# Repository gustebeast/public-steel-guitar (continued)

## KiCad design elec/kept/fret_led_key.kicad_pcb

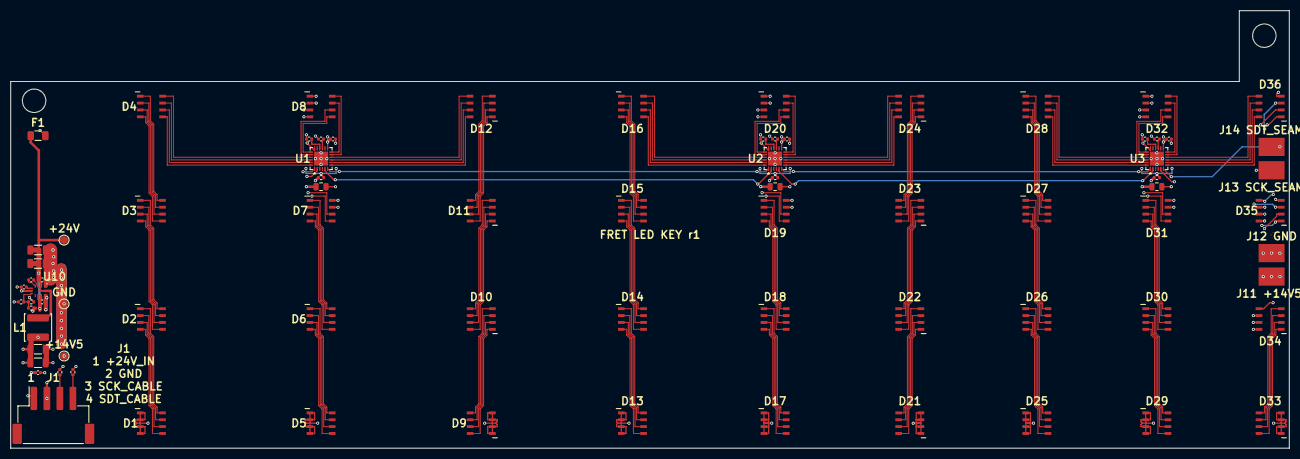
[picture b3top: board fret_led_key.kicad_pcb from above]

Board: 4 copper layers, 245.5 x 84.0 mm, 79 parts (0 on the bottom side), 171 nets.

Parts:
C1, C2, C3, C34: 1uF/25V; C_0402_1005Metric
C11, C12, C13, C32, C33, C35, C38: 100nF/50V; C_0402_1005Metric
C21, C22, C23: 4.7uF/50V; C_0805_2012Metric
C30, C31, C36, C37: 10uF/50V; C_1206_3216Metric
D1, D2, D3, D4, D5, D6, D7, D8, D9, D10, D11, D12, D13, D14, D15, D16, D17, D18, D19, D20, D21, D22, D23, D24, D25, D26, D27, D28, D29, D30, D31, D32, D33, D34, D35, D36: XL-5050RGBW; XINGLIGHT_XL-5050RGBW
F1: JFC1206-1200FS; Fuse_1206_3216Metric
J1: S4B-XH-SM4-TB; JST_XH_S4B-XH-SM4-TB_1x04-1MP_P2.50mm_Horizontal
J11, J12, J13, J14: YZF0002-38080-02; Xinyangze_YZF0002-38080-02
L1: SWPA5040S4R7MT; L_Sunlord_SWPA5040S
R1, R2, R3: 3k3; R_0402_1005Metric
R10: 100k 1%; R_0402_1005Metric
R11: 7k68 1%; R_0402_1005Metric
R12: 200k 1%; R_0402_1005Metric
R21, R22: 1k 1%; R_0402_1005Metric
R41, R42, R43: 0R; R_0402_1005Metric
TP1, TP2, TP3: TP; TestPoint_Pad_D1.5mm
U1, U2, U3: TLC5971RGER; Texas_RGE0024H_VQFN-24-1EP_4x4mm_P0.5mm_EP2.7x2.7mm
U10: LMR33630BRNXR; Texas_RNX0012_VQFN-HR-12_2x3mm_P0.5mm

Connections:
+14V5: C11.1, C12.1, C13.1, C21.1, C22.1, C23.1, C36.1, C37.1, C38.1, J11.1, L1.2, R10.1, R41.1, R42.1, R43.1, TP2.1, U1.13, U2.13, U3.13
+24V: C30.1, C31.1, C32.1, C35.1, F1.2, TP1.1, U10.2, U10.9, U10.10
+24V_IN: F1.1, J1.1
BOOT: C33.1, U10.4
BUCK_VCC: C34.1, U10.5
FB: R10.2, R11.1, R12.1, U10.7
FEED1: D1.1, D1.2, D1.3, D1.4, D5.1, D5.2, D5.3, D5.4, D9.1, D9.2, D9.3, D9.4, R41.2
FEED2: D13.1, D13.2, D13.3, D13.4, D17.1, D17.2, D17.3, D17.4, D21.1, D21.2, D21.3, D21.4, R42.2
FEED3: D25.1, D25.2, D25.3, D25.4, D29.1, D29.2, D29.3, D29.4, D33.1, D33.2, D33.3, D33.4, R43.2
GND: C1.2, C2.2, C3.2, C11.2, C12.2, C13.2, C21.2, C22.2, C23.2, C30.2, C31.2, C32.2, C34.2, C35.2, C36.2, C37.2, C38.2, J1.2, J12.1, R1.2, R2.2, R3.2, R11.2, R12.2, TP3.1, U1.18, U1.25, U2.18, U2.25, U3.18, U3.25, U10.1, U10.6, U10.11
IREF1: R1.1, U1.16
IREF2: R2.1, U2.16
IREF3: R3.1, U3.16
SCK_1: U1.5, U2.2
SCK_2: U2.5, U3.2
SCK_CABLE: J1.3, R21.1
SCK_IN: R21.2, U1.2
SCK_SEAM: J13.1, U3.5
SDT_1: U1.6, U2.1
SDT_2: U2.6, U3.1
SDT_CABLE: J1.4, R22.1
SDT_IN: R22.2, U1.1
SDT_SEAM: J14.1, U3.6
SW: C33.2, L1.1, U10.3, U10.12
VREG1: C1.1, U1.15
VREG2: C2.1, U2.15
VREG3: C3.1, U3.15
Z1_B_0: D1.7, D2.3
Z1_B_1: D2.7, D3.3
Z1_B_2: D3.7, D4.3
Z1_B_RET: D4.7, U1.23
Z1_G_0: D1.6, D2.2
Z1_G_1: D2.6, D3.2
Z1_G_2: D3.6, D4.2
Z1_G_RET: D4.6, U1.22
Z1_R_0: D1.5, D2.1
Z1_R_1: D2.5, D3.1
Z1_R_2: D3.5, D4.1
Z1_R_RET: D4.5, U1.21
Z1_W_0: D1.8, D2.4
Z1_W_1: D2.8, D3.4
Z1_W_2: D3.8, D4.4
Z1_W_RET: D4.8, U1.24
Z2_B_0: D5.7, D6.3
Z2_B_1: D6.7, D7.3
Z2_B_2: D7.7, D8.3
Z2_B_RET: D8.7, U1.20
Z2_G_0: D5.6, D6.2
Z2_G_1: D6.6, D7.2
Z2_G_2: D7.6, D8.2
Z2_G_RET: D8.6, U1.12
Z2_R_0: D5.5, D6.1
Z2_R_1: D6.5, D7.1
Z2_R_2: D7.5, D8.1
Z2_R_RET: D8.5, U1.11
Z2_W_0: D5.8, D6.4
Z2_W_1: D6.8, D7.4
Z2_W_2: D7.8, D8.4
Z2_W_RET: D8.8, U1.19
Z3_B_0: D9.7, D10.3
Z3_B_1: D10.7, D11.3
Z3_B_2: D11.7, D12.3
Z3_B_RET: D12.7, U1.9
Z3_G_0: D9.6, D10.2
Z3_G_1: D10.6, D11.2
Z3_G_2: D11.6, D12.2
Z3_G_RET: D12.6, U1.8
Z3_R_0: D9.5, D10.1
Z3_R_1: D10.5, D11.1
Z3_R_2: D11.5, D12.1
Z3_R_RET: D12.5, U1.7
Z3_W_0: D9.8, D10.4
Z3_W_1: D10.8, D11.4
Z3_W_2: D11.8, D12.4
Z3_W_RET: D12.8, U1.10
Z4_B_0: D13.7, D14.3
Z4_B_1: D14.7, D15.3
Z4_B_2: D15.7, D16.3
Z4_B_RET: D16.7, U2.23
Z4_G_0: D13.6, D14.2
Z4_G_1: D14.6, D15.2
Z4_G_2: D15.6, D16.2
Z4_G_RET: D16.6, U2.22
Z4_R_0: D13.5, D14.1
Z4_R_1: D14.5, D15.1
Z4_R_2: D15.5, D16.1
Z4_R_RET: D16.5, U2.21
Z4_W_0: D13.8, D14.4
Z4_W_1: D14.8, D15.4
Z4_W_2: D15.8, D16.4
Z4_W_RET: D16.8, U2.24
Z5_B_0: D17.7, D18.3
Z5_B_1: D18.7, D19.3
Z5_B_2: D19.7, D20.3
Z5_B_RET: D20.7, U2.20
Z5_G_0: D17.6, D18.2
Z5_G_1: D18.6, D19.2
Z5_G_2: D19.6, D20.2
Z5_G_RET: D20.6, U2.12
Z5_R_0: D17.5, D18.1
Z5_R_1: D18.5, D19.1
Z5_R_2: D19.5, D20.1
Z5_R_RET: D20.5, U2.11
Z5_W_0: D17.8, D18.4
Z5_W_1: D18.8, D19.4
Z5_W_2: D19.8, D20.4
Z5_W_RET: D20.8, U2.19
Z6_B_0: D21.7, D22.3
Z6_B_1: D22.7, D23.3
Z6_B_2: D23.7, D24.3
Z6_B_RET: D24.7, U2.9
Z6_G_0: D21.6, D22.2
Z6_G_1: D22.6, D23.2
Z6_G_2: D23.6, D24.2
Z6_G_RET: D24.6, U2.8
Z6_R_0: D21.5, D22.1
Z6_R_1: D22.5, D23.1
Z6_R_2: D23.5, D24.1
Z6_R_RET: D24.5, U2.7
Z6_W_0: D21.8, D22.4
Z6_W_1: D22.8, D23.4
Z6_W_2: D23.8, D24.4
Z6_W_RET: D24.8, U2.10
Z7_B_0: D25.7, D26.3
Z7_B_1: D26.7, D27.3
Z7_B_2: D27.7, D28.3
Z7_B_RET: D28.7, U3.23
Z7_G_0: D25.6, D26.2
Z7_G_1: D26.6, D27.2
Z7_G_2: D27.6, D28.2
Z7_G_RET: D28.6, U3.22
Z7_R_0: D25.5, D26.1
Z7_R_1: D26.5, D27.1
Z7_R_2: D27.5, D28.1
Z7_R_RET: D28.5, U3.21
Z7_W_0: D25.8, D26.4
Z7_W_1: D26.8, D27.4
Z7_W_2: D27.8, D28.4
Z7_W_RET: D28.8, U3.24
Z8_B_0: D29.7, D30.3
Z8_B_1: D30.7, D31.3
Z8_B_2: D31.7, D32.3
Z8_B_RET: D32.7, U3.20
Z8_G_0: D29.6, D30.2
Z8_G_1: D30.6, D31.2
Z8_G_2: D31.6, D32.2
Z8_G_RET: D32.6, U3.12
Z8_R_0: D29.5, D30.1
Z8_R_1: D30.5, D31.1
Z8_R_2: D31.5, D32.1
Z8_R_RET: D32.5, U3.11
Z8_W_0: D29.8, D30.4
Z8_W_1: D30.8, D31.4
Z8_W_2: D31.8, D32.4
Z8_W_RET: D32.8, U3.19
Z9_B_0: D33.7, D34.3
Z9_B_1: D34.7, D35.3
Z9_B_2: D35.7, D36.3
Z9_B_RET: D36.7, U3.9
Z9_G_0: D33.6, D34.2
Z9_G_1: D34.6, D35.2
Z9_G_2: D35.6, D36.2
Z9_G_RET: D36.6, U3.8
Z9_R_0: D33.5, D34.1
Z9_R_1: D34.5, D35.1
Z9_R_2: D35.5, D36.1
Z9_R_RET: D36.5, U3.7
Z9_W_0: D33.8, D34.4
Z9_W_1: D34.8, D35.4
Z9_W_2: D35.8, D36.4
Z9_W_RET: D36.8, U3.10

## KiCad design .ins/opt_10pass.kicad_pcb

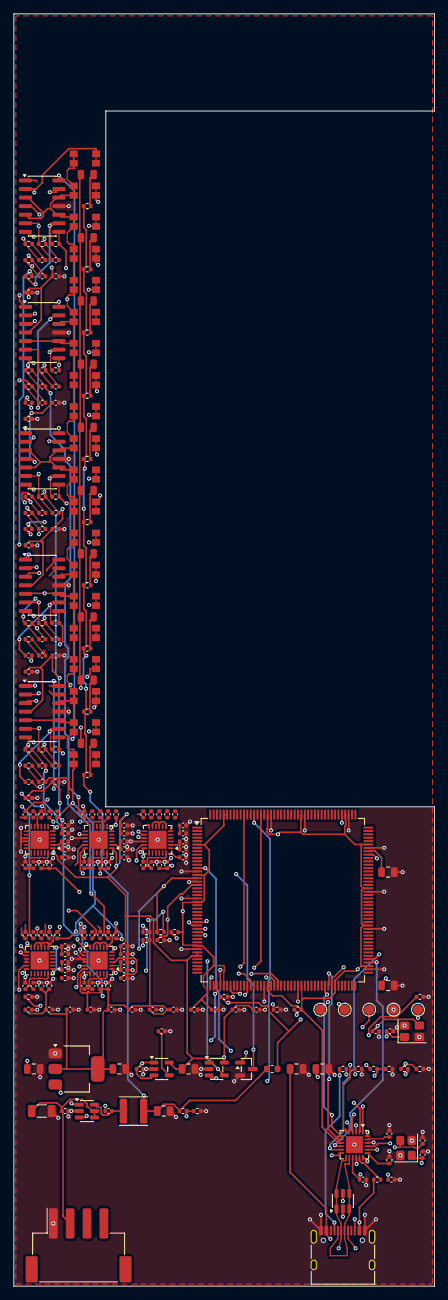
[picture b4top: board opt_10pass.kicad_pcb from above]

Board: 4 copper layers, 62.3 x 188.5 mm, 241 parts (0 on the bottom side), 148 nets.

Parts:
C100, C101, C102, C103, C104, C105, C106, C107, C108, C109, C110, C111, C121, C140, C141, C142, C143, C161, C163: 100nF; C_0402_1005Metric
C112, C113: 2.2uF; C_0805_2012Metric
C120, C122, C127: 1uF; C_0402_1005Metric
C123, C124: 27pF; C_0402_1005Metric
C125, C126: 30pF; C_0402_1005Metric
C130: 100nF; C_0805_2012Metric
C131, C132, C133: 10uF; C_0805_2012Metric
C160: 10uF/50V; C_1206_3216Metric
C162: 22uF/16V; C_0805_2012Metric
C164: 10uF/16V; C_0805_2012Metric
Cd11, Cd12, Cd21, Cd22, Cd31, Cd32, Cd41, Cd42, Cd51, Cd52: 100nF; C_0402_1005Metric
Cf11, Cf12, Cf13, Cf14, Cf21, Cf22, Cf23, Cf24, Cf31, Cf32, Cf33, Cf34, Cf41, Cf42, Cf43, Cf44, Cf51, Cf52, Cf53, Cf54: 1pF; C_0402_1005Metric
Ci11, Ci12, Ci13, Ci14, Ci21, Ci22, Ci23, Ci24, Ci31, Ci32, Ci33, Ci34, Ci41, Ci42, Ci43, Ci44, Ci51, Ci52, Ci53, Ci54: 10nF C0G; C_0402_1005Metric
Cm1, Cm2, Cm3, Cm4, Cm5: 100nF; C_0402_1005Metric
Cs11, Cs15, Cs21, Cs25, Cs31, Cs35, Cs41, Cs45, Cs51, Cs55: 1uF; C_0402_1005Metric
Cs12, Cs14, Cs17, Cs19, Cs22, Cs24, Cs27, Cs29, Cs32, Cs34, Cs37, Cs39, Cs42, Cs44, Cs47, Cs49, Cs52, Cs54, Cs57, Cs59: 100nF; C_0402_1005Metric
Cs13, Cs16, Cs18, Cs23, Cs26, Cs28, Cs33, Cs36, Cs38, Cs43, Cs46, Cs48, Cs53, Cs56, Cs58: 10uF; C_0402_1005Metric
D1, D2, D3, D4, D5, D6, D7, D8, D9, D10: IR17-21C/TR8; LED_0805_2012Metric
FB1: GZ1608D601TF; L_0603_1608Metric
J1: TYPE-C-31-M-12; USB_C_Receptacle_HRO_TYPE-C-31-M-12
J2: S4B-XH-SM4-TB; JST_XH_S4B-XH-SM4-TB_1x04-1MP_P2.50mm_Horizontal
L1: SWPA4020S150MT; L_Sunlord_SWPA4020S
PD1A, PD1B, PD2A, PD2B, PD3A, PD3B, PD4A, PD4B, PD5A, PD5B, PD6A, PD6B, PD7A, PD7B, PD8A, PD8B, PD9A, PD9B, PD10A, PD10B: PD15-22B/TR8; Everlight_PD15-22B
Q1: AO3400A; SOT-23
R1, R2, R3, R4, R5, R6, R7, R8, R9, R10: 180R; R_0402_1005Metric
R30, R31: 10k; R_0402_1005Metric
R32, R33: 5k1; R_0402_1005Metric
R34: 9k09 1%; R_0402_1005Metric
R35: 1k 1%; R_0402_1005Metric
R36: 100R; R_0402_1005Metric
R37: 8k06 1%; R_0402_1005Metric
R38, R54: 100k; R_0402_1005Metric
R39: 20k; R_0402_1005Metric
R40: 40k2 1%; R_0402_1005Metric
R41: 10k 1%; R_0402_1005Metric
R50, R51, R52, R53: 4k7; R_0402_1005Metric
Rf11, Rf12, Rf13, Rf14, Rf21, Rf22, Rf23, Rf24, Rf31, Rf32, Rf33, Rf34, Rf41, Rf42, Rf43, Rf44, Rf51, Rf52, Rf53, Rf54: 1M; R_0402_1005Metric
TP1, TP2, TP3, TP4, TP5: SWD; TestPoint_Pad_D1.5mm
U1, U2, U3, U4, U5: TLV9064IDR; SOIC-14_3.9x8.7mm_P1.27mm
U6: STM32H743IIT6; LQFP-176_24x24mm_P0.5mm
U7: USB3343-CP; HVQFN-24-1EP_4x4mm_P0.5mm_EP2.5x2.5mm
U8: AMS1117-3.3; SOT-223-3_TabPin2
U9: SPX3819M5-L-3-3/TR; SOT-23-5
U10: USBLC6-2SC6; SOT-23-6
U11: TLV9061IDBVR; SOT-23-5
U13: TPS560430XFDBVR; SOT-23-6
U14, U15, U16, U17, U18: TLV320ADC3140IRTWT; Texas_RTW_WQFN-24-1EP_4x4mm_P0.5mm_EP2.7x2.7mm
Y1: TX322525M4LBDD2T; Crystal_SMD_3225-4Pin_3.2x2.5mm
Y2: K3A260002010; Crystal_SMD_3225-4Pin_3.2x2.5mm

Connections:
+3V3A: C110.1, C111.1, C132.1, Cd11.1, Cd12.1, Cd21.1, Cd22.1, Cd31.1, Cd32.1, Cd41.1, Cd42.1, Cd51.1, Cd52.1, Cs11.1, Cs12.1, Cs21.1, Cs22.1, Cs31.1, Cs32.1, Cs41.1, Cs42.1, Cs51.1, Cs52.1, R34.1, U1.4, U2.4, U3.4, U4.4, U5.4, U6.38, U6.39, U9.5, U11.5, U14.1, U15.1, U16.1, U17.1, U18.1
+3V3D: C100.1, C101.1, C102.1, C103.1, C104.1, C105.1, C106.1, C107.1, C108.1, C109.1, C121.1, C131.1, Cs18.1, Cs19.1, Cs28.1, Cs29.1, Cs38.1, Cs39.1, Cs48.1, Cs49.1, Cs58.1, Cs59.1, R31.2, R50.2, R51.2, R52.2, R53.2, TP5.1, U6.6, U6.15, U6.23, U6.36, U6.49, U6.62, U6.72, U6.82, U6.91, U6.103, U6.114, U6.127, U6.136, U6.149, U6.159, U6.171, U6.172, U7.9, U7.16, U7.22, U8.2, U14.19, U15.16, U15.19, U16.15, U16.19, U17.15, U17.16, U17.19, U18.19
+5V: C140.1, C141.1, C142.1, C143.1, FB1.2, U9.1, U9.3
+24V: C160.1, C161.1, J2.2, U13.4, U13.5
ADC1_AREG: Cs13.1, Cs14.1, U14.2
ADC1_DREG: Cs16.1, Cs17.1, U14.24
ADC1_IN1P: Ci11.2, U14.6
ADC1_IN2P: Ci12.2, U14.8
ADC1_IN3P: Ci13.2, U14.10
ADC1_IN4P: Ci14.2, U14.12
ADC1_INM: Cm1.2, U14.7, U14.9, U14.11, U14.13
ADC1_VREF: Cs15.1, U14.3
ADC2_AREG: Cs23.1, Cs24.1, U15.2
ADC2_DREG: Cs26.1, Cs27.1, U15.24
ADC2_IN1P: Ci21.2, U15.6
ADC2_IN2P: Ci22.2, U15.8
ADC2_IN3P: Ci23.2, U15.10
ADC2_IN4P: Ci24.2, U15.12
ADC2_INM: Cm2.2, U15.7, U15.9, U15.11, U15.13
ADC2_VREF: Cs25.1, U15.3
ADC3_AREG: Cs33.1, Cs34.1, U16.2
ADC3_DREG: Cs36.1, Cs37.1, U16.24
ADC3_IN1P: Ci31.2, U16.6
ADC3_IN2P: Ci32.2, U16.8
ADC3_IN3P: Ci33.2, U16.10
ADC3_IN4P: Ci34.2, U16.12
ADC3_INM: Cm3.2, U16.7, U16.9, U16.11, U16.13
ADC3_VREF: Cs35.1, U16.3
ADC4_AREG: Cs43.1, Cs44.1, U17.2
ADC4_DREG: Cs46.1, Cs47.1, U17.24
ADC4_IN1P: Ci41.2, U17.6
ADC4_IN2P: Ci42.2, U17.8
ADC4_IN3P: Ci43.2, U17.10
ADC4_IN4P: Ci44.2, U17.12
ADC4_INM: Cm4.2, U17.7, U17.9, U17.11, U17.13
ADC4_VREF: Cs45.1, U17.3
ADC5_AREG: Cs53.1, Cs54.1, U18.2
ADC5_DREG: Cs56.1, Cs57.1, U18.24
ADC5_IN1P: Ci51.2, U18.6
ADC5_IN2P: Ci52.2, U18.8
ADC5_IN3P: Ci53.2, U18.10
ADC5_IN4P: Ci54.2, U18.12
ADC5_INM: Cm5.2, U18.7, U18.9, U18.11, U18.13
ADC5_VREF: Cs55.1, U18.3
ADC_SHDNZ: R54.1, U6.18, U14.14, U15.14, U16.14, U17.14, U18.14
BOOT: C163.1, U13.1
BOOT0: R30.1, U6.166
FB: R40.2, R41.1, U13.3
GND: C100.2, C101.2, C102.2, C103.2, C104.2, C105.2, C106.2, C107.2, C108.2, C109.2, C110.2, C111.2, C112.2, C113.2, C120.2, C121.2, C122.2, C123.2, C124.2, C125.2, C126.2, C127.2, C130.2, C131.2, C132.2, C133.2, C140.2, C141.2, C142.2, C143.2, C160.2, C161.2, C162.2, C164.2, Cd11.2, Cd12.2, Cd21.2, Cd22.2, Cd31.2, Cd32.2, Cd41.2, Cd42.2, Cd51.2, Cd52.2, Cs11.2, Cs12.2, Cs13.2, Cs14.2, Cs15.2, Cs16.2, Cs17.2, Cs18.2, Cs19.2, Cs21.2, Cs22.2, Cs23.2, Cs24.2, Cs25.2, Cs26.2, Cs27.2, Cs28.2, Cs29.2, Cs31.2, Cs32.2, Cs33.2, Cs34.2, Cs35.2, Cs36.2, Cs37.2, Cs38.2, Cs39.2, Cs41.2, Cs42.2, Cs43.2, Cs44.2, Cs45.2, Cs46.2, Cs47.2, Cs48.2, Cs49.2, Cs51.2, Cs52.2, Cs53.2, Cs54.2, Cs55.2, Cs56.2, Cs57.2, Cs58.2, Cs59.2, J1.A1, J1.A12, J1.B1, J1.B12, J1.SH, J2.1, Q1.2, R30.2, R32.2, R33.2, R35.2, R37.2, R38.2, R41.2, R54.2, TP4.1, U1.11, U2.11, U3.11, U4.11, U5.11, U6.14, U6.22, U6.37, U6.48, U6.61, U6.71, U6.90, U6.102, U6.113, U6.126, U6.135, U6.148, U6.158, U7.25, U8.1, U9.2, U10.2, U11.2, U13.2, U14.4, U14.15, U14.16, U14.25, U15.4, U15.15, U15.25, U16.4, U16.16, U16.25, U17.4, U17.25, U18.4, U18.15, U18.16, U18.25, Y1.2, Y1.4, Y2.2, Y2.4
I2C2_SCL: R50.1, U6.17, U14.17, U15.17, U16.17, U17.17
I2C2_SDA: R51.1, U6.16, U14.18, U15.18, U16.18, U17.18
I2C4_SCL: R52.1, U6.64, U18.17
I2C4_SDA: R53.1, U6.65, U18.18
LDO_BYP: C127.1, U9.4
LED_A1: D1.2, R1.2
LED_A2: D2.2, R2.2
LED_A3: D3.2, R3.2
LED_A4: D4.2, R4.2
LED_A5: D5.2, R5.2
LED_A6: D6.2, R6.2
LED_A7: D7.2, R7.2
LED_A8: D8.2, R8.2
LED_A9: D9.2, R9.2
LED_A10: D10.2, R10.2
LED_GATE: R36.1, R38.1, U6.161
LED_GATE_Q: Q1.1, R36.2
LED_ROW: D1.1, D2.1, D3.1, D4.1, D5.1, D6.1, D7.1, D8.1, D9.1, D10.1, Q1.3
MID: C133.1, Cm1.1, Cm2.1, Cm3.1, Cm4.1, Cm5.1, PD1A.1, PD1B.1, PD2A.1, PD2B.1, PD3A.1, PD3B.1, PD4A.1, PD4B.1, PD5A.1, PD5B.1, PD6A.1, PD6B.1, PD7A.1, PD7B.1, PD8A.1, PD8B.1, PD9A.1, PD9B.1, PD10A.1, PD10B.1, U1.3, U1.5, U1.10, U1.12, U2.3, U2.5, U2.10, U2.12, U3.3, U3.5, U3.10, U3.12, U4.3, U4.5, U4.10, U4.12, U5.3, U5.5, U5.10, U5.12, U11.1, U11.4
MID_RAW: R34.2, R35.1, U11.3
NRST: R31.1, TP3.1, U6.31
OSC_IN: C123.1, U6.29, Y1.1
OSC_OUT: C124.1, U6.30, Y1.3
PHY_1V8: C122.1, U7.23
PHY_RBIAS: R37.1, U7.19
PHY_VBUS: R39.2, U7.17
PHY_VDD33: C120.1, U7.15, U7.18
PHY_XI: C125.1, U7.21, Y2.1
PHY_XO: C126.1, U7.20, Y2.3
SAI_FS: U6.3, U14.23, U15.23, U16.23, U17.23, U18.23
SAI_SCK: U6.4, U14.22, U15.22, U16.22, U17.22, U18.22
SAI_SD1: U6.5, U14.21
SAI_SD2: U6.2, U15.21
SAI_SD3: U6.40, U16.21
SAI_SD4: U6.175, U17.21
SAI_SD5: U6.143, U18.21
SW: C163.2, L1.1, U13.6
SWCLK: TP2.1, U6.137
SWDIO: TP1.1, U6.124
TIA_IN_1A: Cf11.1, PD1A.2, Rf11.1, U1.2
TIA_IN_1B: Cf12.1, PD1B.2, Rf12.1, U1.6
TIA_IN_2A: Cf13.1, PD2A.2, Rf13.1, U1.9
TIA_IN_2B: Cf14.1, PD2B.2, Rf14.1, U1.13
TIA_IN_3A: Cf21.1, PD3A.2, Rf21.1, U2.2
TIA_IN_3B: Cf22.1, PD3B.2, Rf22.1, U2.6
TIA_IN_4A: Cf23.1, PD4A.2, Rf23.1, U2.9
TIA_IN_4B: Cf24.1, PD4B.2, Rf24.1, U2.13
TIA_IN_5A: Cf31.1, PD5A.2, Rf31.1, U3.2
TIA_IN_5B: Cf32.1, PD5B.2, Rf32.1, U3.6
TIA_IN_6A: Cf33.1, PD6A.2, Rf33.1, U3.9
TIA_IN_6B: Cf34.1, PD6B.2, Rf34.1, U3.13
TIA_IN_7A: Cf41.1, PD7A.2, Rf41.1, U4.2
TIA_IN_7B: Cf42.1, PD7B.2, Rf42.1, U4.6
TIA_IN_8A: Cf43.1, PD8A.2, Rf43.1, U4.9
TIA_IN_8B: Cf44.1, PD8B.2, Rf44.1, U4.13
TIA_IN_9A: Cf51.1, PD9A.2, Rf51.1, U5.2
TIA_IN_9B: Cf52.1, PD9B.2, Rf52.1, U5.6
TIA_IN_10A: Cf53.1, PD10A.2, Rf53.1, U5.9
TIA_IN_10B: Cf54.1, PD10B.2, Rf54.1, U5.13
TIA_OUT_1A: Cf11.2, Ci11.1, Rf11.2, U1.1
TIA_OUT_1B: Cf12.2, Ci12.1, Rf12.2, U1.7
TIA_OUT_2A: Cf13.2, Ci13.1, Rf13.2, U1.8
TIA_OUT_2B: Cf14.2, Ci14.1, Rf14.2, U1.14
TIA_OUT_3A: Cf21.2, Ci21.1, Rf21.2, U2.1
TIA_OUT_3B: Cf22.2, Ci22.1, Rf22.2, U2.7
TIA_OUT_4A: Cf23.2, Ci23.1, Rf23.2, U2.8
TIA_OUT_4B: Cf24.2, Ci24.1, Rf24.2, U2.14
TIA_OUT_5A: Cf31.2, Ci31.1, Rf31.2, U3.1
TIA_OUT_5B: Cf32.2, Ci32.1, Rf32.2, U3.7
TIA_OUT_6A: Cf33.2, Ci33.1, Rf33.2, U3.8
TIA_OUT_6B: Cf34.2, Ci34.1, Rf34.2, U3.14
TIA_OUT_7A: Cf41.2, Ci41.1, Rf41.2, U4.1
TIA_OUT_7B: Cf42.2, Ci42.1, Rf42.2, U4.7
TIA_OUT_8A: Cf43.2, Ci43.1, Rf43.2, U4.8
TIA_OUT_8B: Cf44.2, Ci44.1, Rf44.2, U4.14
TIA_OUT_9A: Cf51.2, Ci51.1, Rf51.2, U5.1
TIA_OUT_9B: Cf52.2, Ci52.1, Rf52.2, U5.7
TIA_OUT_10A: Cf53.2, Ci53.1, Rf53.2, U5.8
TIA_OUT_10B: Cf54.2, Ci54.1, Rf54.2, U5.14
ULPI_CK: U6.51, U7.2
ULPI_D0: U6.47, U7.4
ULPI_D1: U6.56, U7.5
ULPI_D2: U6.57, U7.6
ULPI_D3: U6.79, U7.7
ULPI_D4: U6.80, U7.8
ULPI_D5: U6.92, U7.10
ULPI_D6: U6.93, U7.11
ULPI_D7: U6.163, U7.12
ULPI_DIR: U6.13, U7.1
ULPI_NXT: U6.45, U7.3
ULPI_STP: U6.32, U7.24
USB_CC1: J1.A5, R32.1
USB_CC2: J1.B5, R33.1
USB_DM: J1.A7, J1.B7, U7.14, U10.3, U10.4
USB_DP: J1.A6, J1.B6, U7.13, U10.1, U10.6
V5_PRE: C162.1, C164.1, FB1.1, L1.2, R1.1, R2.1, R3.1, R4.1, R5.1, R6.1, R7.1, R8.1, R9.1, R10.1, R40.1, U8.3
VBUS: C130.1, J1.A4, J1.A9, J1.B4, J1.B9, R39.1, U10.5
VCAP1: C112.1, U6.81
VCAP2: C113.1, U6.125

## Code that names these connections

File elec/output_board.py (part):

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    map it used there (SAI1 A/B + SAI2 A/B + SAI3 A, all on SAI1's clocks), so the lock-in
    firmware carries over; no USB3300, no ULPI. It is a FULL-SPEED DEVICE to the brain board's
    CM5 (J9, OTG_FS on PA11/PA12). It also REPLACES THE CH32V307: it clocks both audio
    converters (SAI4, PF6-PF9 + PB2), drives the relay, the jack mode and the gain pot. The hub (CH334F) and the CH340
    flash path are gone: the H743's ROM DFU loader lives on OTG_FS, so the CM5 flashes
    it over J9 (USB-only firmware rule); BOOT0 has a pad for recovery.
  * DUAL USB-C POWER + DATA (work item R2-6). J1 and J2 each sink USB PD (5-20 V; EPR is
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MCU_IO = {
    # THE OPTICAL LANES, exactly the optical board's map (optical.py SAI_CLK / SAI_SD): 192 kHz,
    # BCLK 12.288 MHz, one lane per converter, SAI2 and SAI3 synchronous slaves of SAI1
    "SAI_SCK": "PE5",       # SAI1_SCK_A
    "SAI_FS": "PE4",        # SAI1_FS_A
    "SAI_SD1": "PE6",       # SAI1_SD_A   <- optical U15
    "SAI_SD2": "PE3",       # SAI1_SD_B   <- U16
    "SAI_SD3": "PA0",       # SAI2_SD_B   <- U17
    "SAI_SD4": "PI6",       # SAI2_SD_A   <- U18
    "SAI_SD5": "PD1",       # SAI3_SD_A   <- U19
    "OPT_EMIT": "PB3",      # TIM2_CH2: the emitter gate, frequency-locked to FSYNC (optical.py)
    # SAI4 for the 48 kHz audio converters, its own clock domain: block B master-transmit to
    # the DAC, block A synchronous to block B receiving the ADC (SAI4's A clock pins are
    # PE4/PE5 only, which the optical lanes hold)
    "I2S_CK": "PF8",        # SAI4_SCK_B
    "I2S_WS": "PF9",        # SAI4_FS_B
    "I2S_SDO": "PF6",       # SAI4_SD_B   -> PCM5102A DIN
    "I2S_SDI": "PB2",       # SAI4_SD_A   <- PCM1808 DOUT
    "I2S_MCK": "PF7",       # SAI4_MCLK_B
    "MCU_DM": "PA11",       # OTG_FS_DM -> J9, the brain board's CM5
    "MCU_DP": "PA12",       # OTG_FS_DP
    # three I2C buses: the two AP33772S share the fixed address 0x52, so each has its own
    "PDA_SCL": "PB6", "PDA_SDA": "PB7",          # I2C1 AF4 -> U13, port J1
    "PDB_SCL": "PH7", "PDB_SDA": "PH8",          # I2C3 AF4 -> U14, port J2
    "I2C2_SDA": "PF0", "I2C2_SCL": "PF1",        # I2C2 AF4 -> U16 INA226 (as optical)
    # the gain pot on SPI4 (or bit-banged: three plain outputs)
    "POT_CS": "PE11", "POT_SCK": "PE12", "POT_SDI": "PE14",
    "RELAY": "PD8", "JACK_MODE": "PD9",
    "PDA_INT": "PD10", "PDB_INT": "PD11",        # AP33772S INT: push-pull, HIGH = event; FT pins
    "INA_ALERT_N": "PD12",
    "OPT_VBUS_EN": "PD13", "OPT_FAULT_N": "PG2",
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              "gate, 5 V (1.27 mm 2x10 vertical, HX PZ1.27 family as J5 on the brain)",
              footprint="Connector_PinHeader_1.27mm:PinHeader_2x10_P1.27mm_Vertical_SMD",
              pins=[Pin(num=n, func=P) for n in range(1, 21)])
    for pin, net in ((1, opt_5v), (2, opt_5v), (3, gnd), (4, io["SAI_SCK"]), (5, gnd),
                     (6, io["SAI_FS"]), (7, gnd), (8, io["SAI_SD1"]), (9, io["SAI_SD2"]),
                     (10, gnd), (11, io["SAI_SD3"]), (12, io["SAI_SD4"]), (13, gnd),
                     (14, io["SAI_SD5"]), (15, gnd), (16, io["OPT_EMIT"]), (17, gnd),
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    gnd += u1[PIN["VSSA"]]
    v3d += (u1[PIN["VDDA"]], u1[PIN["VREF+"]], u1[PIN["VBAT"]], u1[PIN["VDD33_USB"]],
            u1[PIN["PDR_ON"]])
    osc_in += u1[PIN["PH0"]]
    osc_out += u1[PIN["PH1"]]
    nrst += u1[PIN["NRST"]]
    boot0 += u1[PIN["BOOT0"]]
    swdio, swclk = Net("SWDIO"), Net("SWCLK")
    swdio += u1[PIN["PA13"]]
    swclk += u1[PIN["PA14"]]
    vcap1, vcap2 = Net("VCAP1"), Net("VCAP2")
    vcap1 += u1[PIN["VCAP1"]]
    vcap2 += u1[PIN["VCAP2"]]
    # ⚠ THE AP33772S INT IS A 5 V PUSH-PULL OUTPUT (from its V5V) and PD10 / PD11 are FT pins,
    # whose limit is VDD + 4 V: 4.0 V with the H743 unpowered, which the charger side can
    # outlive at start-up (voltage_check FAIL, 2026-11-13). Each INT reaches its pin through a
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        io[name] += u1[PIN[port]]
    used = (set(MCU_VDD) | set(MCU_VSS)
            | {PIN[k] for k in ("VSSA", "VDDA", "VREF+", "VBAT", "VDD33_USB", "PDR_ON", "PH0",
                                "PH1", "NRST", "BOOT0", "PA13", "PA14", "VCAP1", "VCAP2")}
            | {PIN[p] for p in MCU_IO.values()})
    for n in mcu_pins:
        if n not in used:
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    _res("R5", "100R", "relay gate series", relay, q1[1])
    _res("R36", "100k", "relay gate pull-down -- off through reset", q1[1], gnd)
    _res("R37", "100k", "JACK_MODE pull-down -- balanced through reset: on the MCU side, "
         "where the pin floats; U34 is the F part, LOW on an open input", io["JACK_MODE"], gnd)
    _res("R8", "1M", "pickup input bias to VMID -- and the LOAD the pickup sees, which "
         "sets its tone: 1M is a typical amplifier input", pk_in, vmid)
    _res("R9", "220R", "output series -- bounds a phantom-power fault and C1's inrush",
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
